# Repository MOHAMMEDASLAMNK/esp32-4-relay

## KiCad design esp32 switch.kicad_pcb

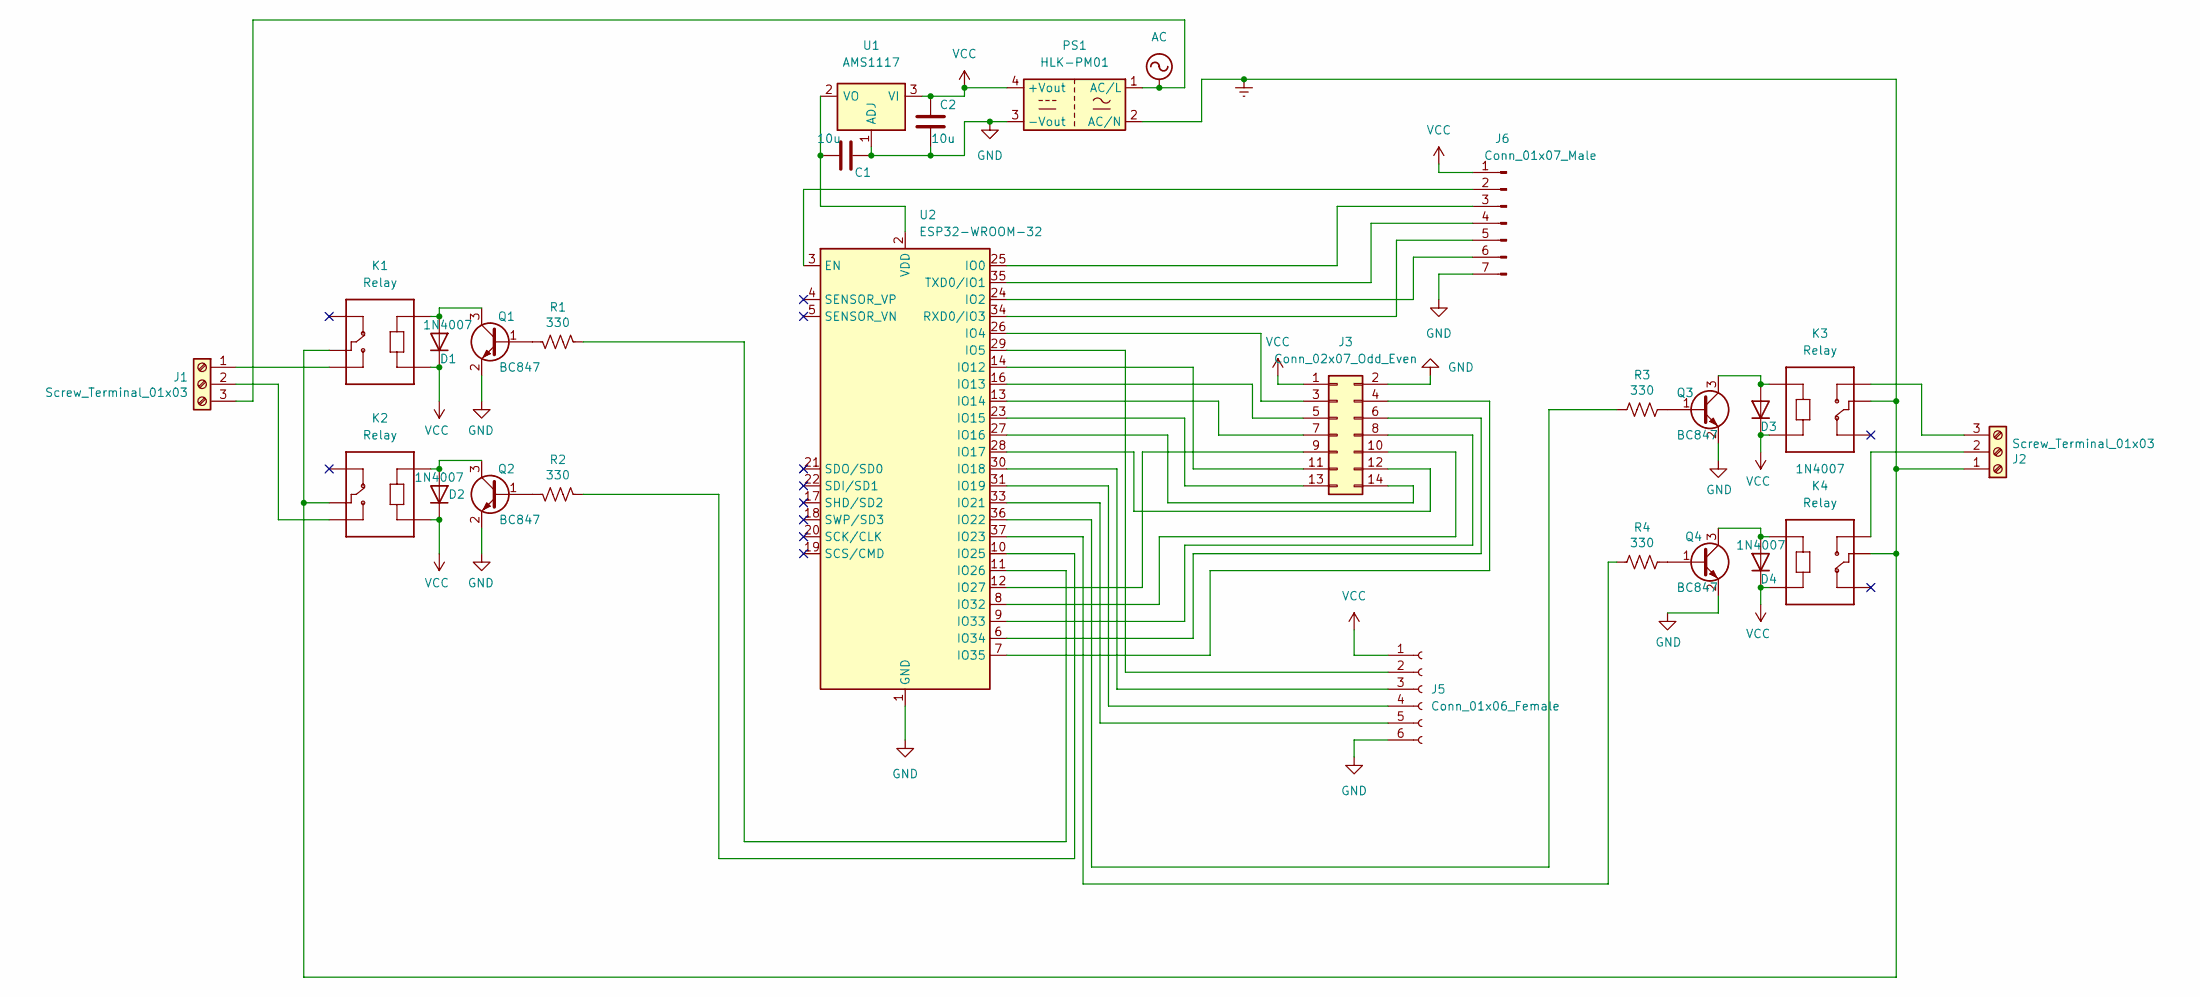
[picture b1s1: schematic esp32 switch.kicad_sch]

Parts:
C1, C2: 10u; C_0805_2012Metric_Pad1.18x1.45mm_HandSolder
D1, D2, D3, D4: 1N4007; D_SOD-123
J1, J2: Screw_Terminal_01x03; TerminalBlock_Altech_AK300-3_P5.00mm
J3: Conn_02x07_Odd_Even; IDC-Header_2x07_P2.54mm_Vertical
J5: Conn_01x06_Female; JST_EH_B6B-EH-A_1x06_P2.50mm_Vertical
J6: Conn_01x07_Male; PinHeader_1x07_P2.54mm_Vertical
K1, K2, K3, K4: Relay; RELAY_SRD-05VDC-SL-C
PS1: HLK-PM01; Converter_ACDC_CHEAP
Q1, Q2, Q3, Q4: BC847; SOT-23
R1, R2, R3, R4: 330; R_0805_2012Metric_Pad1.20x1.40mm_HandSolder
U1: AMS1117; SOT-223-3_TabPin2
U2: ESP32-WROOM-32

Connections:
AC: J1.3, PS1.1 (AC/L)
Earth: J2.1, K1.COM, K2.COM, K3.COM, K4.COM, PS1.2 (AC/N)
GND: C1.2, C2.2, J3.2, J5.6, J6.7, PS1.3 (-Vout), Q1.2 (E), Q2.2 (E), Q3.2 (E), Q4.2 (E), U1.1 (ADJ), U2.1 (GND), U2.15 (GND), U2.38 (GND), U2.39 (GND)
unnamed: C1.1, U1.2 (VO), U2.2 (VDD)
unnamed: D1.2 (A), K1.A2, Q1.3 (C)
unnamed: D2.2 (A), K2.A2, Q2.3 (C)
unnamed: D3.2 (A), K3.A1, Q3.3 (C)
unnamed: D4.2 (A), K4.A1, Q4.3 (C)
unnamed: J2.2, K4.NO
unnamed: J2.3, K3.NO
unnamed: J3.3, U2.26 (IO4)
unnamed: J3.4, U2.7 (IO35)
unnamed: J3.5, U2.16 (IO13)
unnamed: J3.6, U2.6 (IO34)
unnamed: J3.7, U2.13 (IO14)
unnamed: J3.8, U2.9 (IO33)
unnamed: J3.9, U2.12 (IO27)
unnamed: J3.10, U2.8 (IO32)
unnamed: J3.11, U2.14 (IO12)
unnamed: J3.12, U2.28 (IO17)
unnamed: J3.13, U2.23 (IO15)
unnamed: J3.14, U2.27 (IO16)
unnamed: J5.2, U2.29 (IO5)
unnamed: J5.3, U2.30 (IO18)
unnamed: J5.4, U2.31 (IO19)
unnamed: J5.5, U2.33 (IO21)
unnamed: J6.2, U2.3 (EN)
unnamed: J6.3, U2.25 (IO0)
unnamed: J6.4, U2.35 (TXD0/IO1)
unnamed: J6.5, U2.34 (RXD0/IO3)
unnamed: J6.6, U2.24 (IO2)
unnamed: J1.1, K1.NO
unnamed: J1.2, K2.NO
unnamed: Q1.1 (B), R1.1
unnamed: Q2.1 (B), R2.1
unnamed: Q3.1 (B), R3.1
unnamed: Q4.1 (B), R4.1
unnamed: R1.2, U2.11 (IO26)
unnamed: R2.2, U2.10 (IO25)
unnamed: R3.2, U2.36 (IO22)
unnamed: R4.2, U2.37 (IO23)
VCC: C2.1, D1.1 (K), D2.1 (K), D3.1 (K), D4.1 (K), J3.1, J5.1, J6.1, K1.A1, K2.A1, K3.A2, K4.A2, PS1.4 (+Vout), U1.3 (VI)

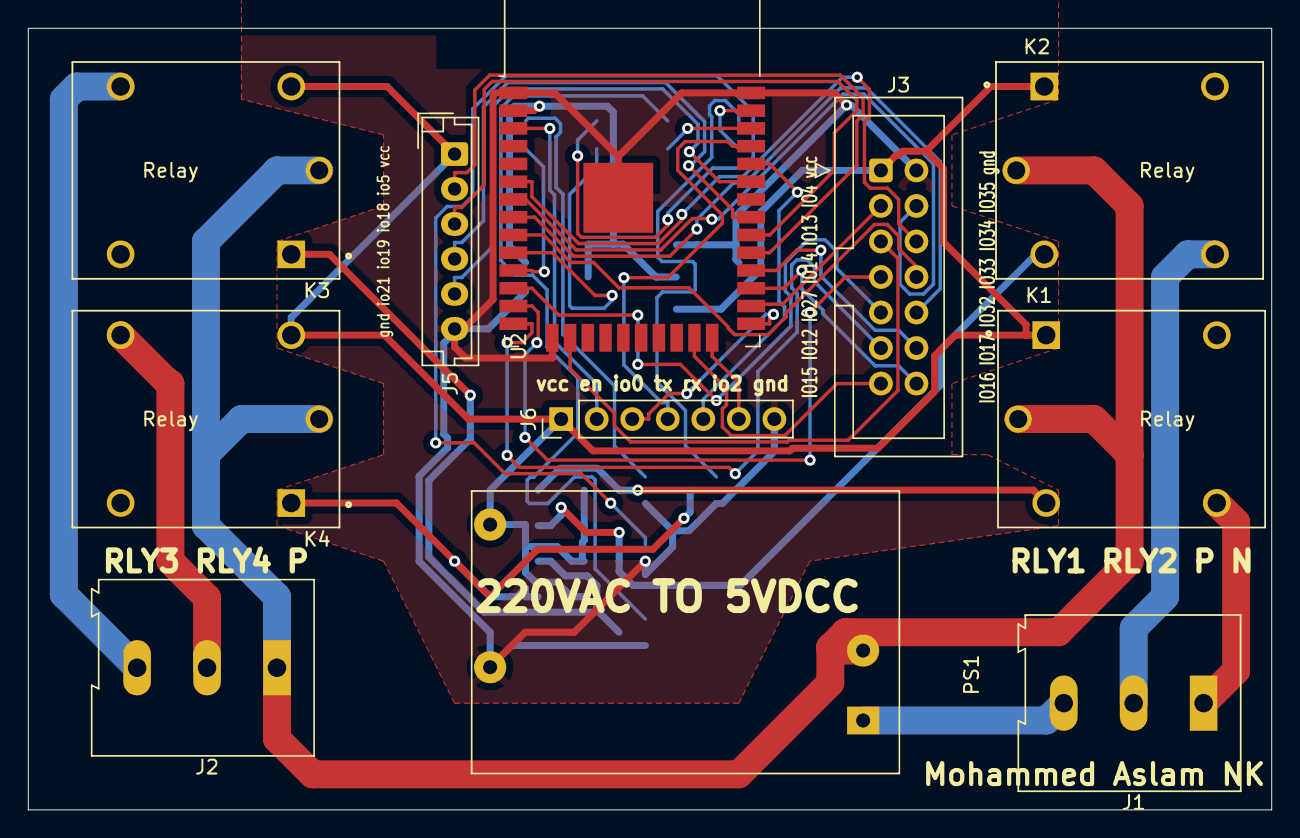
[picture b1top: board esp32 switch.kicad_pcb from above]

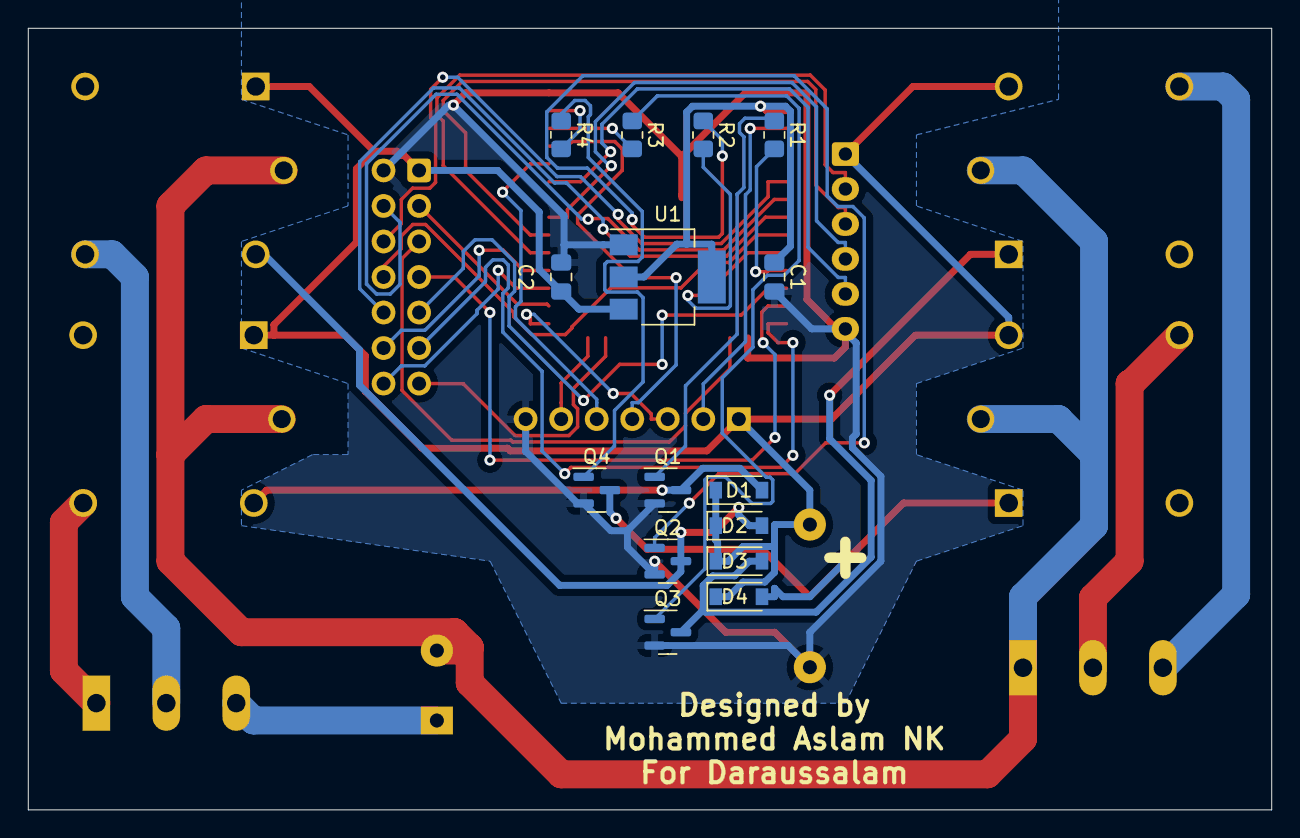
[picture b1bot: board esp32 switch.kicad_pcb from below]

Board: 2 copper layers, 88.9 x 55.9 mm, 26 parts (15 on the bottom side), 42 nets.
